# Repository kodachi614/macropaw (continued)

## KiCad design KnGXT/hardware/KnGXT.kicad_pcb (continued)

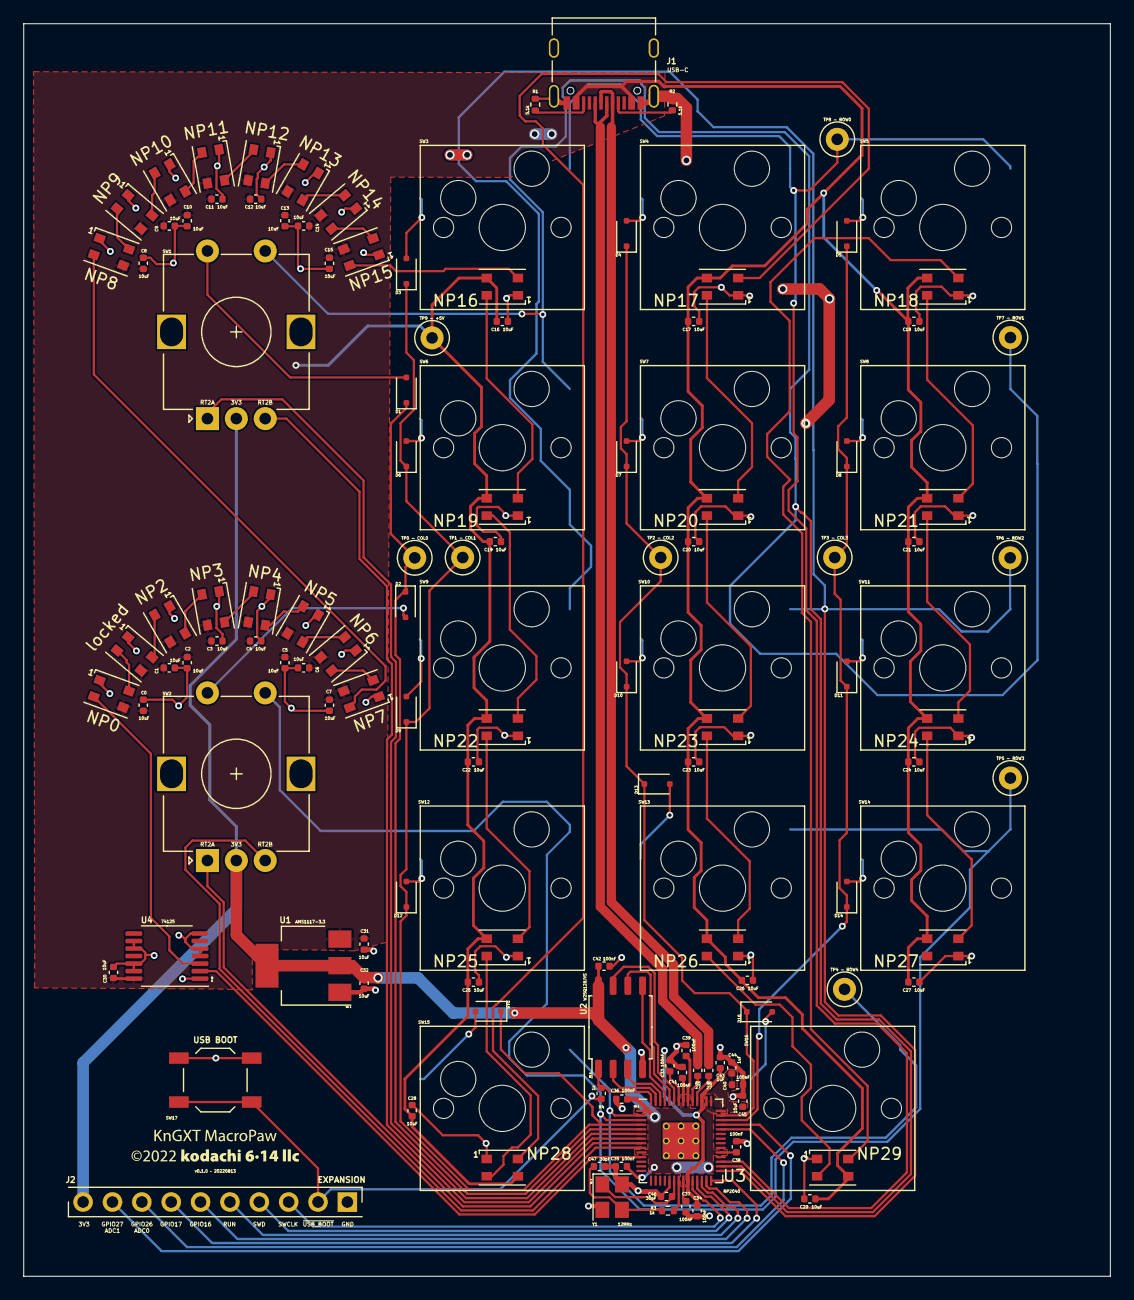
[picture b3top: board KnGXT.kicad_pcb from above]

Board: 2 copper layers, 94.0 x 108.3 mm, 134 parts (0 on the bottom side), 87 nets.

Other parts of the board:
locked: WS2812B; LED XL-3528RGBW-WS2812B (3.5x2.8, C2890364)

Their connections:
+5V: locked.3 (VDD); also elsewhere on the board
GND: locked.1 (VSS); also elsewhere on the board
unnamed 56: locked.2 (DIN); also elsewhere on the board
unnamed 57: locked.4 (DOUT); also elsewhere on the board

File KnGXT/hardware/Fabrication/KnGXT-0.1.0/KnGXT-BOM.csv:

10uF,"C0,C1,C2,C3,C4,C5,C6,C7,C8,C9,C10,C11,C12,C13,C14,C15,C16,C17,C18,C19,C20,C21,C22,C23,C24,C25,C26,C27,C28,C29,C30,C31,C32,C45",0402,C15525
100nF,"C33,C34,C35,C36,C37,C38,C39,C40,C41,C42",0402,C1525
1uF,"C43,C44",0402,C52923
30pF,"C46,C47",0402,C1570
1N4148,"D1,D2,D3,D4,D5,D6,D7,D8,D9,D10,D11,D12,D13,D14,D15,D16",SOD-323F,C2128
USB_C_Receptacle,J1,Palconn_UTC16-G,C165948
WS2812B,"NP0,NP1,NP2,NP3,NP4,NP5,NP6,NP7,NP8,NP9,NP10,NP11,NP12,NP13,NP14,NP15,NP16,NP17,NP18,NP19,NP20,NP21,NP22,NP23,NP24,NP25,NP26,NP27,NP28,NP29",WS2812B 3.5x2.8 (C2890364),C2890364
5.1k Ohm,"R1,R2",0402,C25905
1k Ohm,R3,0402,C11702
1k Ohm,R4,0402,C11702
27 Ohm,"R5,R6",0402,C25100
SW_Push,SW17,SPST_TL3342,C318884
AMS1117-3.3,U1,SOT-223,C6186
W25Q128JVS,U2,SOIC-8 5.23x5.23mm_P1.27mm,C97521
RP2040,U3,QFN-56,C2040
74125,U4,TSSOP-14 4.4x5mm_P0.65mm,C36365
12MHz,Y1,SMD_3225 4Pin 3.2x2.5mm,C9002

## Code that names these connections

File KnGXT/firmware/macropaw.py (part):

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        super().__init__()

        # Pins to use when scanning keys
        self.col_pins = (board.COL0, board.COL1, board.COL2, board.COL3)
        self.row_pins = (board.ROW0, board.ROW1, board.ROW2, board.ROW3, board.ROW4)
        self.diode_orientation = DiodeOrientation.ROW2COL

        # self.allpixels is the underlying LED array of the hardware.
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        # create and register the scanners
        self.matrix = [
            RotaryioEncoder(
                pin_a=board.RT1B,
                pin_b=board.RT1A,
                pull="down",
                divisor=4,
            ),
            RotaryioEncoder(
                pin_a=board.RT2B,
                pin_b=board.RT2A,
                pull="down",
                divisor=4,
            ),
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
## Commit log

2022-08-13 Ignore backups
2022-08-13 Drop the weird XML output
2022-08-13 Don't track ZIPfiles
2022-08-13 Update the world to switch to 3.5x2.8mm WS2812B LEDs
2022-08-14 v0.1.0 fabrication outputs
2022-08-14 Swap the WS2812B _AGAIN_ since the C965557 is out of stock
    Thankfully the C2890364 is identical to the C965557, just
    rotated 180 degrees.
2022-08-14 Add version number
2022-08-14 Rename "Gerber-0.1.0" to "KnGXT-0.1.0"
2022-08-14 Try reformatting the BOM and CPL (including CRLF instead of just LF)
2022-09-05 Move hardware files to hardware/ directory
2022-09-05 Scrap old fp-info-cache file
2022-09-07 Add the hardware license, and update the README to reflect that.
2022-09-07 Update version, date, and license in schematic
2022-10-03 Have a directory per board model.
2022-10-10 Add KiCad libraries
2022-11-07 Add KnGXT MacroPaw firmware
2022-11-07 Makefile and tools
2023-04-02 Toss old kicad-libraries dir in favor of the kodachi614/kicadlib repo
2023-04-12 Commit STLs for KnGXT case model
2023-04-12 (Mostly?) update KnGXT for KiCad 7 and to use kicadlib.
    KnGXT probably still needs work to pass ERC & DRC, but that's OK because any new spin of it will make further changes.
2023-04-12 Add Fusion 360 source for KnGXT case model
2023-04-12 Whitespace fixes for KnGXT
2023-04-12 Update README to discuss models, and not discuss libraries.
2023-04-12 USBDisconnect, not Power
2023-04-12 Update KnGXT boot stack & status-LED brightness
2023-04-12 Cleaner build process
2023-04-12 New MacroPaw KnGYT hardware!
    The KnGYT is a 5x2 minimalist layout. It's really a test of doublesided assembly.
2023-04-12 Tweaks to README
2023-04-12 Clean up Linux build process
2023-04-12 More build + README cleanup
2023-04-12 When building firmware, have the board run the hardware test on first boot.
2023-04-12 Switch to (hackily) versioned link for KnGXT firmware.
2023-04-21 Add MacroPaw KnGYT firmware
2023-04-21 Deal with the fact that unmounting MACROPAW is sometimes slow on MacOS
2023-04-21 GPL 3.0 _or later_
2023-05-25 Make hardware test stick until all the switches have been cycled through all their LED colors. Include a dim white in the initial colors.
2023-05-25 Allow serial communications during hardware test.
2023-05-25 Move animation setup into macropaw.py, to simplify code.py.
2023-05-25 Include DaVinci Resolve and numpad layers.
2023-05-25 Support multiple keymaps using the Keymapper and the /keymap file.
2023-05-25 Logging tools. Why is this so slow to boot?
2023-05-25 Allow switching keymaps using keys.
2023-05-25 Main layer now includes SPACE and ENTER. Make layer names match the upcoming user guide.
2023-05-25 fixup KnGXT code.py
2023-05-25 KnGXT comments
2023-05-25 Update KnGYT firmware with new stuff from KnGXT edits
2023-05-25 Update Makefile and README for multiple MacroPaw models.
2023-06-07 User docs
2023-06-07 Photos for user guides
2025-04-21 Initial Beatboxer (KnH0F) cut
2025-05-06 Update build and build docs
2025-05-06 Clean up hardware test code for KnGXT and KnGYT
2025-05-06 Rename PoliteRGB to MacroPawRGB
2025-05-06 Define (and switch to) the breathmap effect.
2025-05-06 Drop ringrgb.py from KnGYT (it has no LED rings)
2025-05-06 KnGYT case models
2025-05-07 Shouldn't have committed these models in the first place – they're for the KnGYT.
    (So is the firmware, for that matter. Sigh.)
2025-05-07 Add and document tools/flash for MacOS
2025-05-07 Update BUILDING with version info.
2025-05-07 BeatBoxer hardware as fabbed
2025-05-07 CircuitPython stopped supporting setting the stack limit in either 9.x or 10.x.
2025-05-07 Update adafruit_pioasm.mpy to the CircuitPython 9 version
2025-05-07 OMG MacroPawKeyboard never initialized its superclass??
2025-05-07 Drop USBDisconnect for the moment
2025-05-07 Move a bunch of boot code into bootkeys.py and firstboot.py, so that the hardware-dependent part is really just in bootkeys.py.
2025-05-07 Give PixelSlice a deinit method to avoid an error when it's used as an underlying pixel buffer for the KMK RGB extension
2025-05-07 Clean up debug output.
2025-05-07 Port away from Key.clone()
2025-05-07 Port KnGYT to CircuitPython 9.2.7.
2025-05-08 Write a README into the firmware telling what kind of board the firmware is for, and where to find the source.
2025-05-08 Add a slight delay in the TriggerRowCombo check, so that you don't see phantom keypresses in the second check.
    This is a little weird to me; I'm going to have to go figure out what's going on here in hardware...
2025-05-08 Refactor non-hardware-specific stuff into common/
2025-05-08 Update CircuitPython and KMK versions in Makefile
2025-05-08 If mpy-cross is available, use it -- this cuts a ridiculous amount of time off boot.
2025-05-08 Stupid typo fix
2025-05-09 KnH0F Beatboxer support
2025-05-09 Ditch weird MacOS files in build-uf2
2025-05-09 Bump base firmware commit
2025-05-15 Use the HWTEST button for both mass storage mode and hardware test on the Beatboxer KnH0F.
2025-05-15 Beatboxer: Use the breathing animation instead of the knight animation.
2025-05-16 Documentation updates
2025-05-16 Look for mpy-cross anywhere in the PATH
2025-05-16 Update for 0.5.2, using BEATBOX for the Beatboxer's volume name
2025-05-16 Oops. Update version number too.
2025-09-12 Introduce SVGs and Fritzing parts
